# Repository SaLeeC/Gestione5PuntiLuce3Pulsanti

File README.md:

# Gestione5PuntiLuce3Pulsanti
Sistema di gestione per 5 punti luce tramite 3 pulsanti

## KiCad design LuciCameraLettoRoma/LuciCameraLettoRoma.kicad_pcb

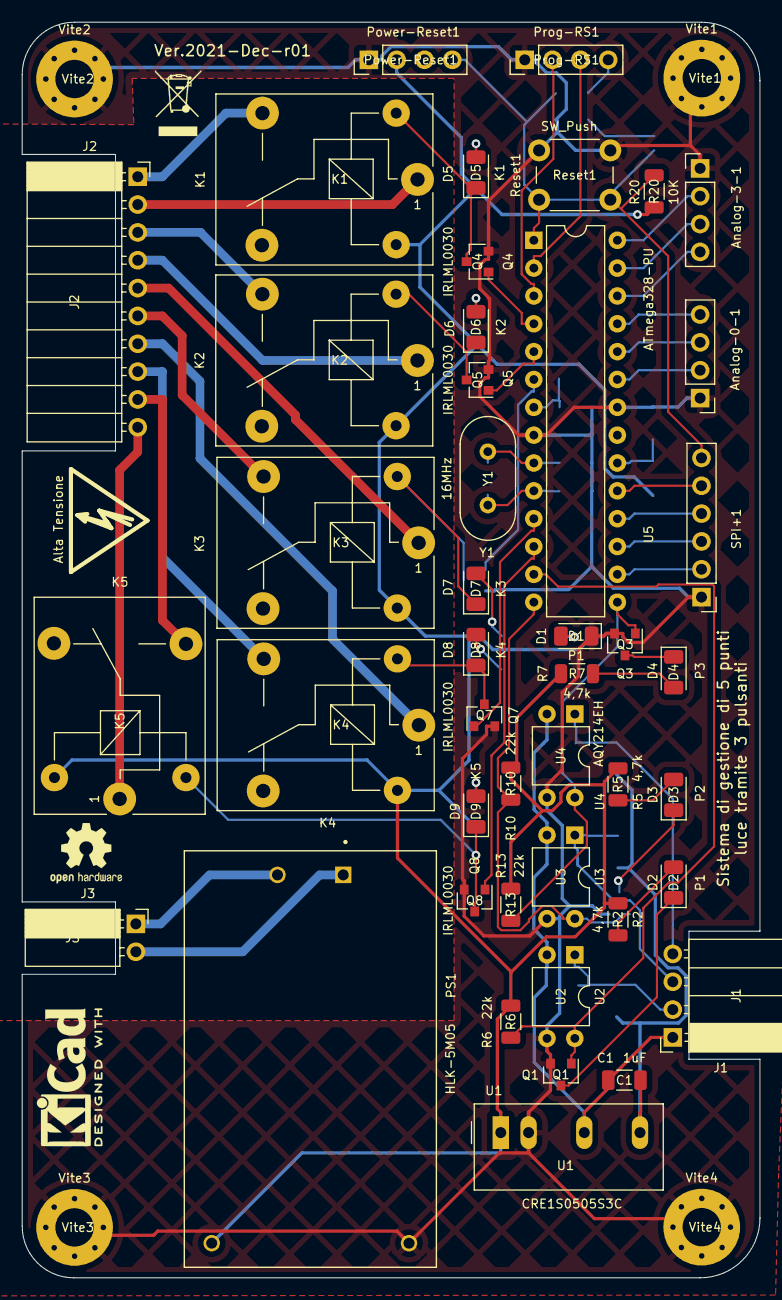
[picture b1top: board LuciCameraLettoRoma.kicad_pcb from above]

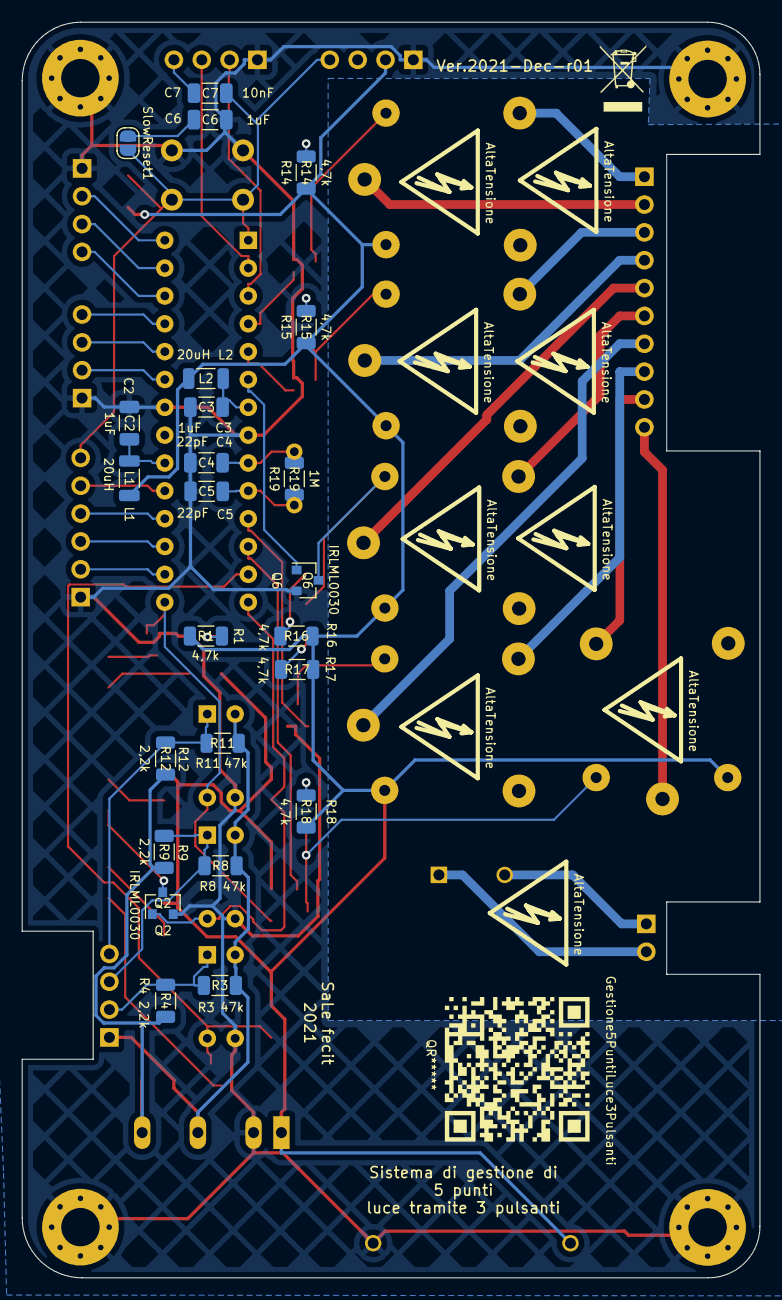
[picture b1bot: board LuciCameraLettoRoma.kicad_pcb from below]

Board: 2 copper layers, 67.3 x 114.6 mm, 87 parts (35 on the bottom side), 63 nets.

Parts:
Alta Tensione: Symbol_HighVoltage_Type2_CopperTop_VerySmall
AltaTensione: Symbol_HighVoltage_Type2_CopperTop_VerySmall
AltaTensione#2, AltaTensione#3, AltaTensione#4, AltaTensione#5, AltaTensione#6, AltaTensione#7, AltaTensione#8, AltaTensione#9: Symbol_HighVoltage_Type2_CopperTop_VerySmall
Analog-0-1, Analog-3-1: PinHeader_1x04_P2.54mm_Vertical
C1, C2, C3, C6: 1uF; C_1206_3216Metric
C4, C5: 22pF; C_1206_3216Metric
C7: 10nF; C_1206_3216Metric
D1, D2: P1; LED_1206_3216Metric
D3: P2; LED_1206_3216Metric
D4: P3; LED_1206_3216Metric
D5: K1; LED_1206_3216Metric
D6: K2; LED_1206_3216Metric
D7: K3; LED_1206_3216Metric
D8: K4; LED_1206_3216Metric
D9: K5; LED_1206_3216Metric
J1: PinSocket_1x04_P2.54mm_Horizontal
J2: PinSocket_1x10_P2.54mm_Horizontal
J3: PinSocket_1x02_P2.54mm_Horizontal
K1, K2, K3, K4, K5: Relay_SPDT_SANYOU_SRD_Series_Form_C
L1, L2: 20uH; L_1206_3216Metric
Logo1: KiCad-Logo2_5mm_SilkScreen
PS1: HLK-5M05; CONV_HLK-5M05
Power-Reset1: PinHeader_1x04_P2.54mm_Vertical
Prog-RS1: PinHeader_1x04_P2.54mm_Vertical
Q1, Q3: SOT-23
Q2, Q4, Q5, Q6, Q7, Q8: IRLML0030; SOT-23
QR*****: Gestione5PuntiLuce3Pulsanti
R1, R2, R5, R7, R14, R15, R16, R17, R18: 4,7k; R_1206_3216Metric
R3, R8, R11: 47k; R_1206_3216Metric
R4, R9, R12: 2,2k; R_1206_3216Metric
R6, R10, R13: 22k; R_1206_3216Metric
R19: 1M; R_1206_3216Metric
R20: 10K; R_1206_3216Metric
REFht1: OSHW-Logo2_7.3x6mm_SilkScreen
Reset1: SW_Push; SW_PUSH_6mm
SPI+1: PinHeader_1x06_P2.54mm_Vertical
SlowReset1: SolderJumper-2_P1.3mm_Open_RoundedPad1.0x1.5mm
U1: CRE1S0505S3C; Converter_DCDC_TRACO_TMR-1-xxxx_Single_THT
U2, U3: DIP-4_W7.62mm
U4: AQY214EH; DIP-4_W7.62mm
U5: ATmega328-PU; DIP-28_W7.62mm
Vite1, Vite2, Vite3, Vite4: MountingHole_3.5mm_Pad_Via
Wast01, Wast02: WEEE-Logo_4.2x6mm_SilkScreen
Y1: 16MHz; Crystal_HC49-U_Vertical

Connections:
+5V: K1.5, K2.5, K3.5, K4.5, K5.5, L1.2, L2.2, PS1.4 (+VO), Power-Reset1.2, R1.1, R2.1, R5.1, R6.2, R7.1, R10.2, R13.2, R14.1, R15.1, R16.1, R17.1, R18.1, R20.1, U1.2 (+VIN)
+5VD: C1.2, R4.1, R9.1, R12.1, U1.4 (+VOUT)
/Luci Camera Letto Roma - Input/Pulsante1-IO: Q1.1 (G), R6.1, U2.4, U5.13 (PD7)
/Luci Camera Letto Roma - Input/Pulsante2-IO: Q2.1 (G), R10.1, U3.4, U5.14 (PB0)
/Luci Camera Letto Roma - Input/Pusante3-IO: Q3.1 (G), R13.1, U4.4, U5.15 (PB1)
/Luci Camera Letto Roma - Rele/Rele-IO2: Q4.1 (G), U5.4 (PD2)
/Luci Camera Letto Roma - Rele/Rele-IO3: Q5.1 (G), U5.5 (PD3)
/Luci Camera Letto Roma - Rele/Rele-IO4: Q6.1 (G), U5.6 (PD4)
/Luci Camera Letto Roma - Rele/Rele-IO5: Q7.1 (G), U5.11 (PD5)
/Luci Camera Letto Roma - Rele/Rele-IO6: Q8.1 (G), U5.12 (PD6)
/Luci Camera Letto Roma CPU/A0: Analog-0-1.2, U5.23 (PC0)
/Luci Camera Letto Roma CPU/A1: Analog-0-1.3, U5.24 (PC1)
/Luci Camera Letto Roma CPU/A2: Analog-0-1.4, U5.25 (PC2)
/Luci Camera Letto Roma CPU/A3: Analog-3-1.4, U5.26 (PC3)
/Luci Camera Letto Roma CPU/A4-I2C-SDA: Analog-3-1.3, U5.27 (PC4)
/Luci Camera Letto Roma CPU/A5-I2C-SCL: Analog-3-1.2, U5.28 (PC5)
/Luci Camera Letto Roma CPU/DTR: C7.2, Prog-RS1.4
/Luci Camera Letto Roma CPU/ICSP-MISO: SPI+1.4, U5.18 (PB4)
/Luci Camera Letto Roma CPU/ICSP-MOSI: SPI+1.3, U5.17 (PB3)
/Luci Camera Letto Roma CPU/ICSP-SCK: SPI+1.5, U5.19 (PB5)
/Luci Camera Letto Roma CPU/IO10-SS: SPI+1.2, U5.16 (PB2)
/Luci Camera Letto Roma CPU/Reset: C7.1, Power-Reset1.4, R20.2, Reset1.1, SPI+1.6, SlowReset1.2 (B), U5.1 (~RESET/PC6)
/Luci Camera Letto Roma CPU/Rx: Prog-RS1.3, U5.2 (PD0)
/Luci Camera Letto Roma CPU/Tx: Prog-RS1.2, U5.3 (PD1)
/Luci Camera Letto Roma CPU/Xtal1: C4.2, R19.2, U5.9 (XTAL1/PB6), Y1.1
/Luci Camera Letto Roma CPU/Xtal2: C5.2, R19.1, U5.10 (XTAL2/PB7), Y1.2
GND: Analog-0-1.1, Analog-3-1.1, C2.1, C3.1, C4.1, C5.1, C6.1, D1.1 (K), PS1.3 (-VO), Power-Reset1.1, Prog-RS1.1, Q1.2 (S), Q2.2 (S), Q3.2 (S), Q4.2 (S), Q5.2 (S), Q6.2 (S), Q7.2 (S), Q8.2 (S), Reset1.2, SPI+1.1, U1.1 (-VIN), U2.3, U3.3, U4.3, U5.8 (GND), U5.22 (GND), Vite1.1, Vite2.1, Vite3.1, Vite4.1
GNDD: C1.1, J1.1, R3.1, R8.1, R11.1, U1.3 (-VOUT), U2.2, U3.2, U4.2
unnamed: C2.2, L1.1, U5.20 (AVCC)
unnamed: C3.2, L2.1, U5.7 (VCC)
unnamed: C6.2, SlowReset1.1 (A)
unnamed: D1.2 (A), R1.2
unnamed: D2.1 (K), Q1.3 (D)
unnamed: D2.2 (A), R2.2
unnamed: D3.1 (K), Q2.3 (D)
unnamed: D3.2 (A), R5.2
unnamed: D4.1 (K), Q3.3 (D)
unnamed: D4.2 (A), R7.2
unnamed: D5.1 (K), K1.2, Q4.3 (D)
unnamed: D5.2 (A), R14.2
unnamed: D6.1 (K), K2.2, Q5.3 (D)
unnamed: D6.2 (A), R15.2
unnamed: D7.1 (K), K3.2, Q6.3 (D)
unnamed: D7.2 (A), R16.2
unnamed: D8.1 (K), K4.2, Q7.3 (D)
unnamed: D8.2 (A), R17.2
unnamed: D9.1 (K), K5.2, Q8.3 (D)
unnamed: D9.2 (A), R18.2
unnamed: J1.2, R3.2, R4.2, U2.1
unnamed: J1.3, R8.2, R9.2, U3.1
unnamed: J1.4, R11.2, R12.2, U4.1
unnamed: J2.1, K1.3
unnamed: J2.2, K1.1
unnamed: J2.3, K2.3
unnamed: J2.4, K2.1
unnamed: J2.9, K5.3
unnamed: J2.10, K5.1
unnamed: J3.1, PS1.2 (AC2)
unnamed: J3.2, PS1.1 (AC1)
unnamed: J2.5, K3.1
unnamed: J2.6, K3.3
unnamed: J2.7, K4.1
unnamed: J2.8, K4.3

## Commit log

2021-12-06 Tanto per iniziare
